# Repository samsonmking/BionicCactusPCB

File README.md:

| Output   | Current Rating (A)|
|----------|-------------------|
|Light     | 3                 |
|Pump Motor| 3                 |

Designed for 2oz Copper / 0.8mm thickness

Made with KiCad Version 4.07. Not yet compatible with version 5.

Download [Schematic PDF](https://github.com/samsonmking/BionicCactusPCB/raw/master/schematic.pdf)

Order on [OshPark here](https://oshpark.com/shared_projects/fiqfBO67)

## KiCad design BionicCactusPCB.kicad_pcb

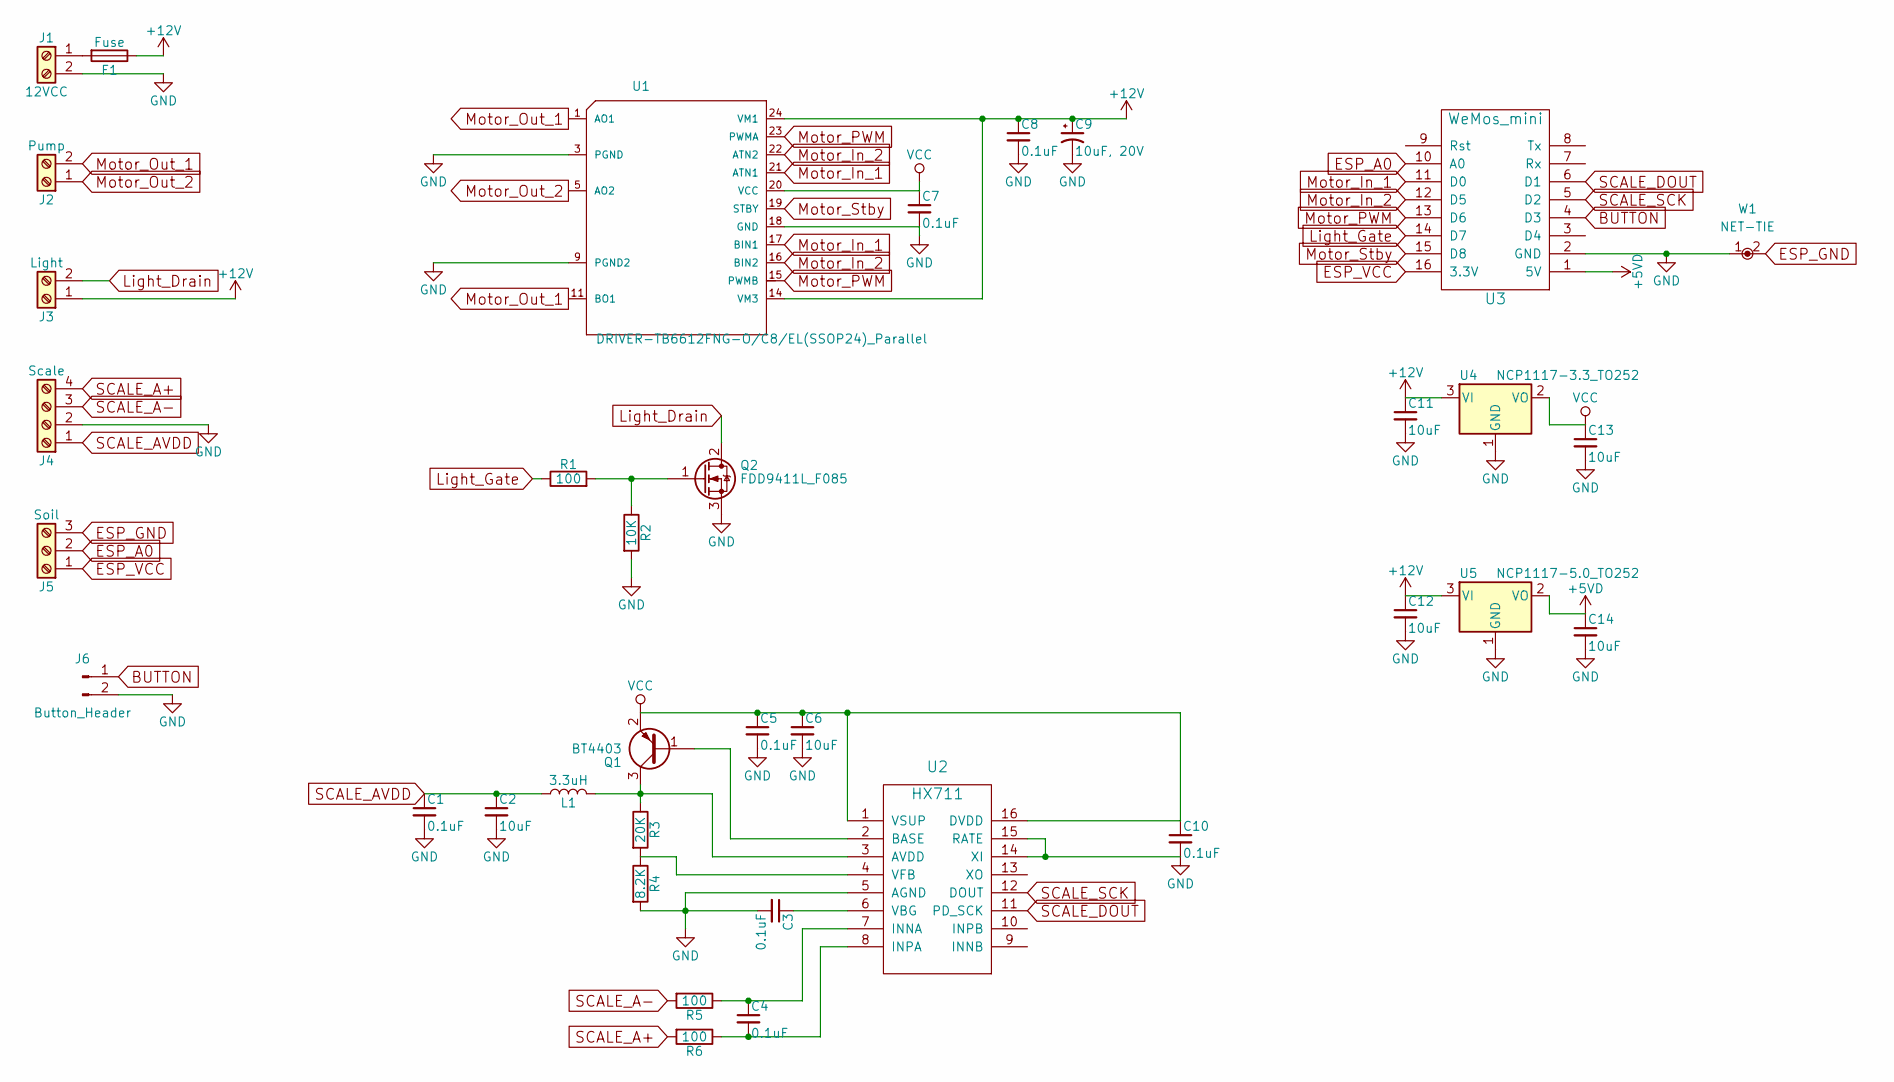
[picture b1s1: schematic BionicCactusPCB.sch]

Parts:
C1, C3, C4, C5, C7, C8, C10: 0.1uF; C_0805_HandSoldering
C2, C6, C11, C12, C13, C14: 10uF; C_1812_HandSoldering
C9: 10uF, 20V; CP_Tantalum_Case-V_EIA-7343-20_Hand
F1: Fuse; BladeFuse-Mini_Keystone_3568
J1: 12VCC; TerminalBlock_bornier-2_P5.08mm
J2: Pump; TerminalBlock_bornier-2_P5.08mm
J3: Light; TerminalBlock_bornier-2_P5.08mm
J4: Scale; TerminalBlock_Phoenix_MPT-2.54mm_4pol
J5: Soil; TerminalBlock_Phoenix_MPT-2.54mm_3pol
J6: Button_Header; Pin_Header_Straight_1x02_Pitch2.54mm
L1: 3.3uH; L_0805_HandSoldering
Q1: BT4403; SOT-23_Handsoldering
Q2: FDD9411L_F085; TO-252-2
R1, R5, R6: 100; R_0805_HandSoldering
R2: 10K; R_0805_HandSoldering
R3: 20K; R_0805_HandSoldering
R4: 8.2K; R_0805_HandSoldering
U1: DRIVER-TB6612FNG-O/C8/EL(SSOP24)_Parallel; SSOP-24_5.3x8.2mm_Pitch0.65mm_tng_mod_parallel
U2: HX711; SOP-16_4.4x10.4mm_Pitch1.27mm
U3: WeMos_mini; D1_mini_board
U4: NCP1117-3.3_TO252; TO-252-2
U5: NCP1117-5.0_TO252; TO-252-2
W1: NET-TIE; NET-TIE-0.3mm

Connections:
+5VD: C14.1, U3.1 (5V), U5.2 (VO)
+12V: C8.1, C9.1, C11.1, C12.1, F1.1, J3.1, U1.14 (VM3), U1.24 (VM1), U4.3 (VI), U5.3 (VI)
BUTTON: J6.1, U3.4 (D3)
ESP_A0: J5.2, U3.10 (A0)
ESP_GND: J5.3, W1.2
ESP_VCC: J5.1, U3.16 (3.3V)
GND: C1.2, C2.2, C3.2, C5.2, C6.2, C7.2, C8.2, C9.2, C10.2, C11.2, C12.2, C13.2, C14.2, J1.2, J4.2, J6.2, Q2.3 (S), R2.2, R4.2, U1.3 (PGND), U1.9 (PGND2), U1.18 (GND), U2.5 (AGND), U2.14 (XI), U2.15 (RATE), U3.2 (GND), U4.1 (GND), U5.1 (GND), W1.1
Light_Drain: J3.2, Q2.2 (D)
Light_Gate: R1.1, U3.14 (D7)
Motor_In_1: U1.17 (BIN1), U1.21 (ATN1), U3.11 (D0)
Motor_In_2: U1.16 (BIN2), U1.22 (ATN2), U3.12 (D5)
Motor_Out_1: J2.2, U1.1 (AO1), U1.11 (BO1)
Motor_Out_2: J2.1, U1.5 (AO2)
Motor_PWM: U1.15 (PWMB), U1.23 (PWMA), U3.13 (D6)
Motor_Stby: U1.19 (STBY), U3.15 (D8)
unnamed: C3.1, U2.6 (VBG)
unnamed: C4.1, R5.1, U2.7 (INNA)
unnamed: C4.2, R6.1, U2.8 (INPA)
unnamed: F1.2, J1.1
unnamed: L1.2, Q1.3 (C), R3.1, U2.3 (AVDD)
unnamed: Q1.1 (B), U2.2 (BASE)
unnamed: Q2.1 (G), R1.2, R2.1
unnamed: R3.2, R4.1, U2.4 (VFB)
SCALE_A+: J4.4, R6.2
SCALE_A-: J4.3, R5.2
SCALE_AVDD: C1.1, C2.1, J4.1, L1.1
SCALE_DOUT: U2.11 (PD_SCK), U3.6 (D1)
SCALE_SCK: U2.12 (DOUT), U3.5 (D2)
VCC: C5.1, C6.1, C7.1, C10.1, C13.1, Q1.2 (E), U1.20 (VCC), U2.1 (VSUP), U2.16 (DVDD), U4.2 (VO)

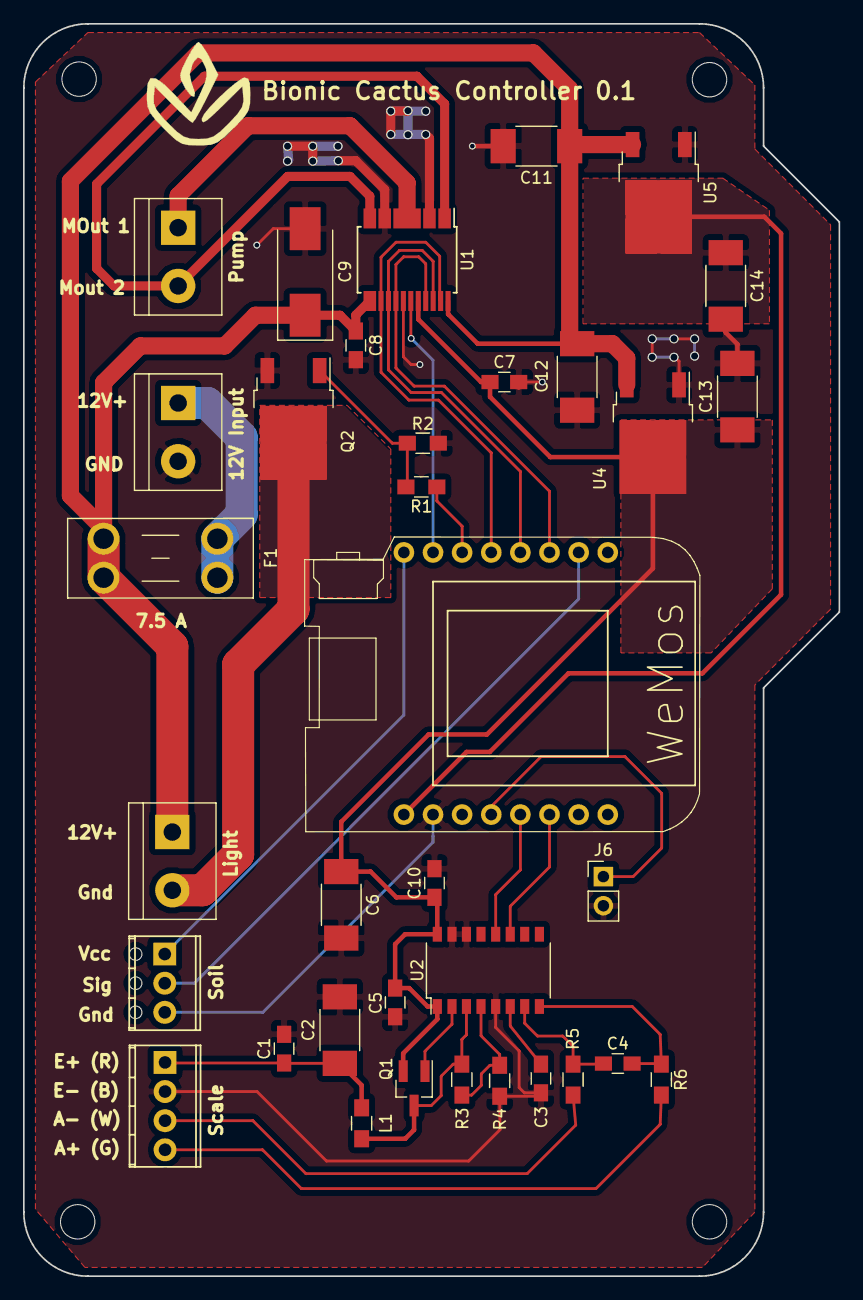
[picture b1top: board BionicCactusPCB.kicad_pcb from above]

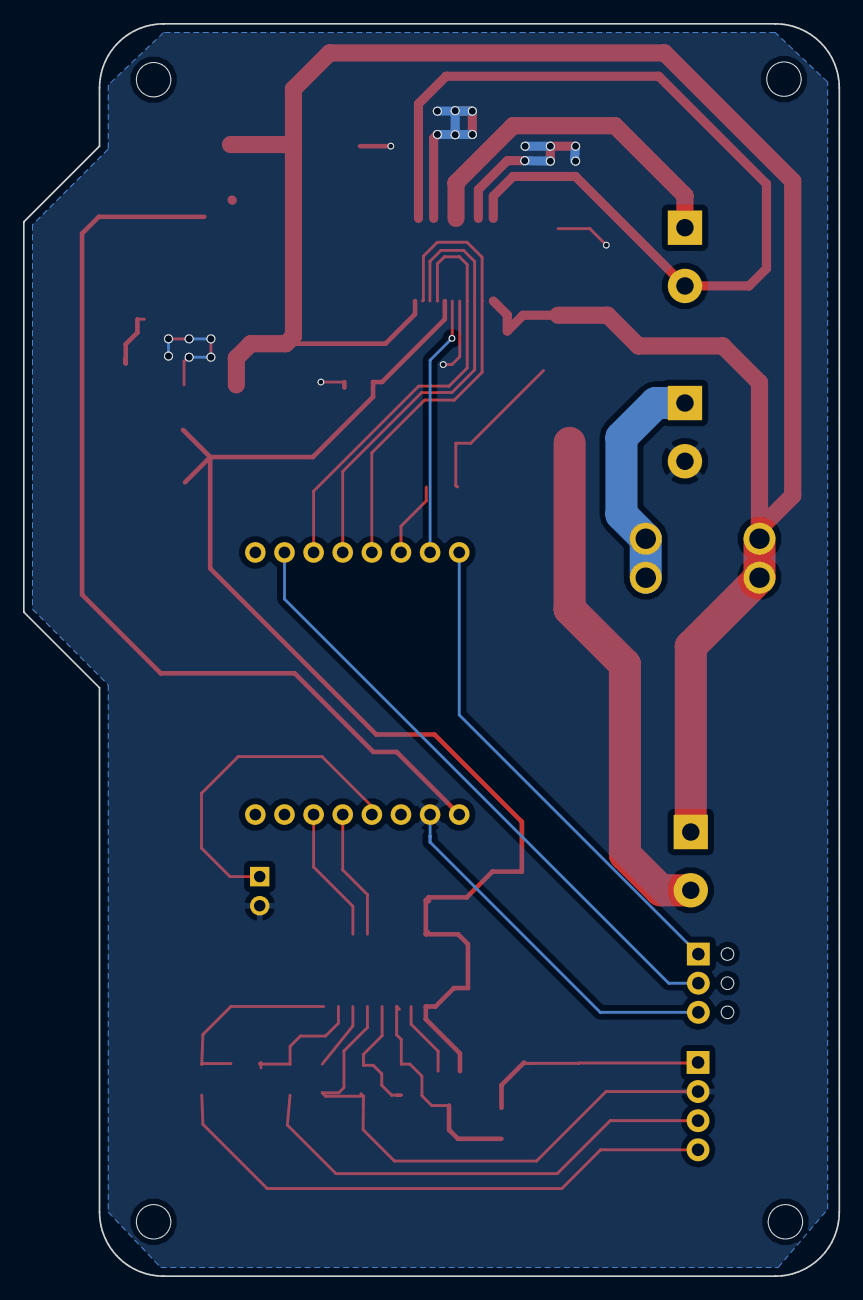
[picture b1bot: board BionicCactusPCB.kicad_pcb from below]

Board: 2 copper layers, 71.1 x 109.2 mm, 36 parts (2 on the bottom side), 29 nets.

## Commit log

2018-12-04 Initial commit working PCB
2019-01-16 Add schematic pdf and net list
2019-01-16 Add README
2019-01-16 Add current and osh park link
